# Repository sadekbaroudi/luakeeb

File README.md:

# Pronunciation

Lua Keyboard (luakeeb)

This is a reversible 95mm x 138mm pcb with support for mx switches (no hotswap), per key led, rotary encoders, and exposes the SDA/SCL/GND/VCC lines in the form of the pimoroni trackball pins (meaning you can add that as well, though the case doesn't support it, so you'll need to devise your own mechanism). It also supports the adafruit qwiic connector, so you can add that connector and access I2C (the sda/scl pins) via a standard format!

See https://www.sparkfun.com/qwiic for details

Note that the 6th column can be broken off. The only thing you need to do is (if using per key leds) solder the jumper near the bottom outside of the board, near the mounting hole. You should solder the jumper on the bottom side of the board (if left half, bottom side of the left half, if right half, bottom side of the right half)

# Support me!

I have spent a lot of time and money designing prototypes, testing, developing, etc. Any contributions would be greatly appreciated!

If you don't want to, or can't afford to support me, please send me a message to let me know you've built one, along with pictures. Also, feel free to submit a pull request with pictures into this repository. I'd be happy to showcase your build.

Reddit: /u/sadekbaroudi
Discord: sadekbaroudi#1258

# Cases

## Split case

You can find the split cases here:
https://github.com/sadekbaroudi/luakeeb/tree/master/cases

I only included the left side, since you can use your slicing software to mirror it to 3d print the right side.

## Monoblock support

This keyboard has the exact same layout as the ffkb ( https://github.com/sadekbaroudi/ffkb )

It was designed in such a way that it is perfectly compatible with the ffkb case. The only considerations are:
* The usb port on ffkb is in the center. In this case, you have two (one for each half). You'll need to cut out a spot on each half to allow you to plug it in.
* The trrs jacks need cut outs as well. However, if you don't care about splitting them up, you can solder the halves together instead of using jacks. In the image below, just solder the outer pins to each other, as indicated by the arrows in the image below.

# Firmware

The general folder for the firmware is here:
https://github.com/sadekbaroudi/qmk_firmware/tree/master/keyboards/fingerpunch/luakeeb/

# Pictures

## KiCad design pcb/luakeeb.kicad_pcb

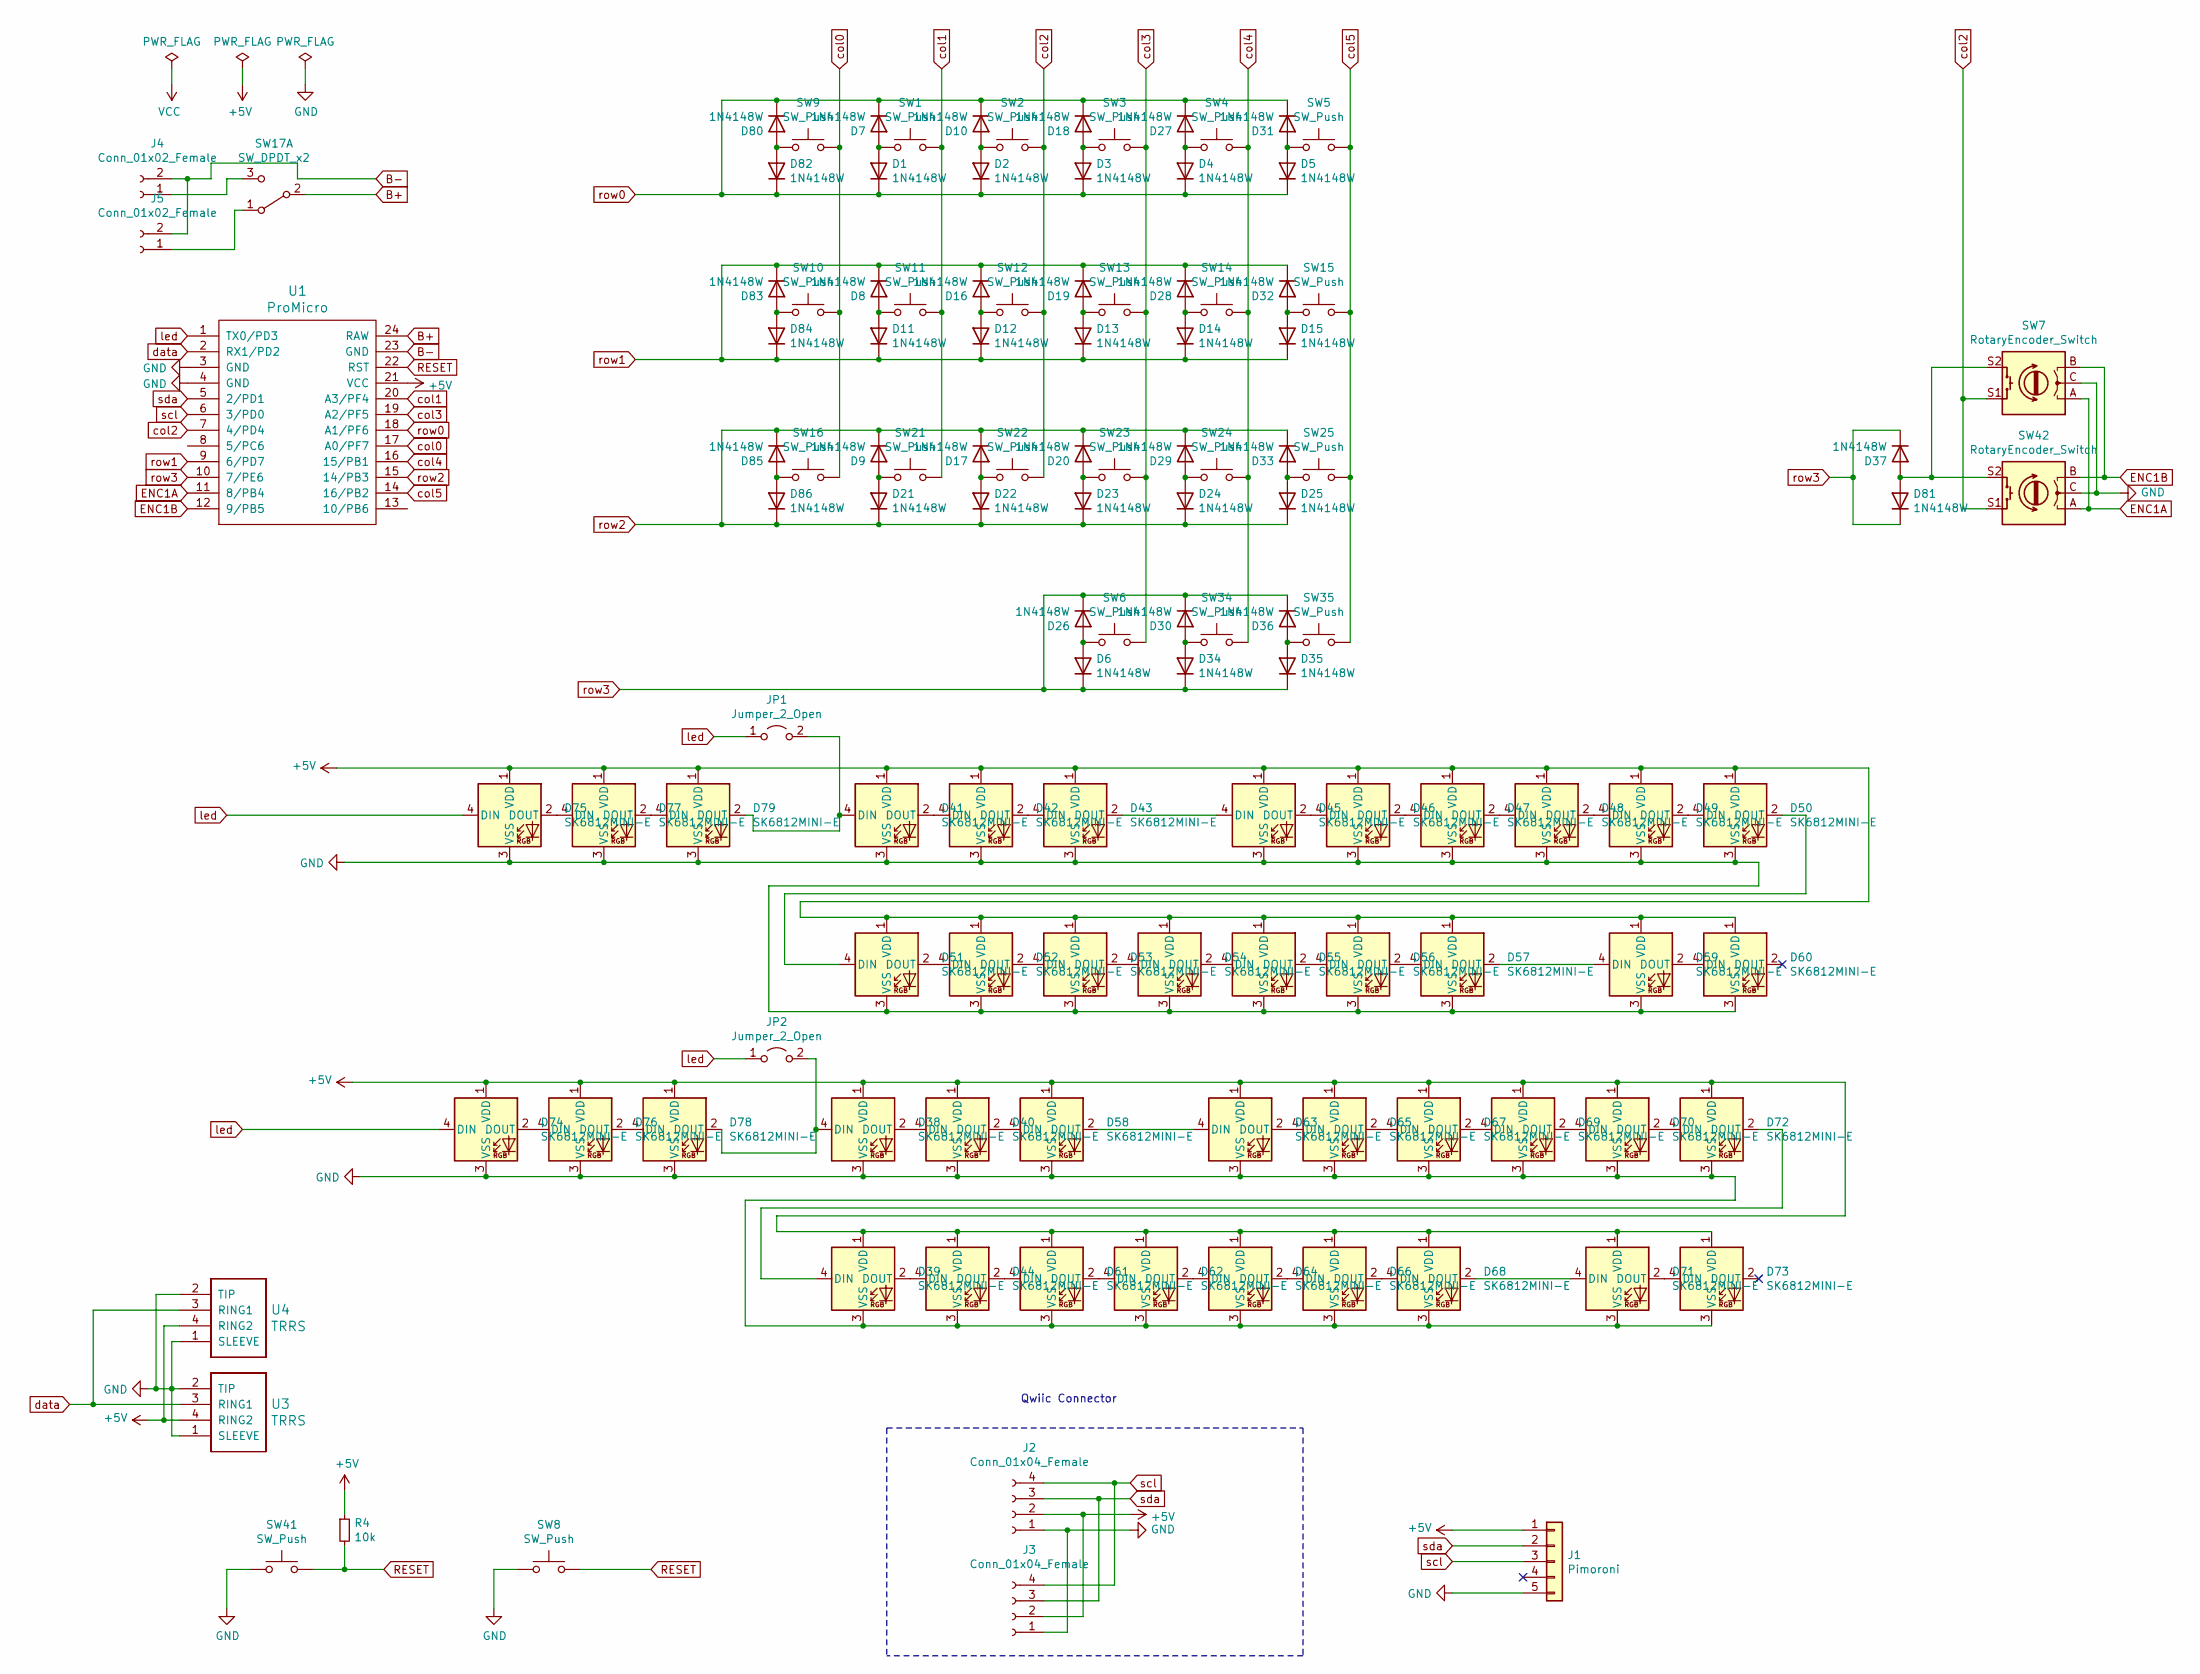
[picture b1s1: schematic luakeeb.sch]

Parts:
D1, D2, D3, D4, D5, D6, D7, D8, D9, D10, D11, D12, D13, D14, D15, D16, D17, D18, D19, D20, D21, D22, D23, D24, D25, D26, D27, D28, D29, D30, D31, D32, D33, D34, D35, D36, D37, D80, D81, D82, D83, D84, D85, D86: 1N4148W; D_SOD-123; LCSC C727110
D38, D39, D40, D41, D42, D43, D44, D45, D46, D47, D48, D49, D50, D51, D52, D53, D54, D55, D56, D57, D58, D59, D60, D61, D62, D63, D64, D65, D66, D67, D68, D69, D70, D71, D72, D73, D74, D75, D76, D77, D78, D79: SK6812MINI-E; MX_SK6812MINI-E
J1: Pimoroni; pimoroni
J2, J3: Conn_01x04_Female; JST_SH_BM04B-SRSS-TB_1x04-1MP_P1.00mm_Vertical
J4, J5: Conn_01x02_Female; JST_PH_S2B-PH-K_1x02_P2.00mm_Horizontal; LCSC C173752
JP1, JP2: Jumper_2_Open; SolderJumper-2_P1.3mm_Open_RoundedPad1.0x1.5mm
R4: 10k; R_0805_2012Metric; LCSC C17414
SW1, SW2, SW3, SW4, SW5, SW6, SW9, SW10, SW11, SW12, SW13, SW14, SW15, SW16, SW21, SW22, SW23, SW24, SW25, SW34, SW35: SW_Push; SW_MX_reversible_minimal
SW7, SW42: RotaryEncoder_Switch; RotaryEncoder_EC11-no-legs
SW8, SW41: SW_Push; SKQG-1155865
SW17: SW_DPDT_x2; SW_CuK_OS102011MA1QN1_SPDT_Angled; LCSC C226259
U1: ProMicro; ArduinoProMicro
U3, U4: TRRS; TRRS-PJ-320A

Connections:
+5V: D38.1 (VDD), D39.1 (VDD), D40.1 (VDD), D41.1 (VDD), D42.1 (VDD), D43.1 (VDD), D44.1 (VDD), D45.1 (VDD), D46.1 (VDD), D47.1 (VDD), D48.1 (VDD), D49.1 (VDD), D50.1 (VDD), D51.1 (VDD), D52.1 (VDD), D53.1 (VDD), D54.1 (VDD), D55.1 (VDD), D56.1 (VDD), D57.1 (VDD), D58.1 (VDD), D59.1 (VDD), D60.1 (VDD), D61.1 (VDD), D62.1 (VDD), D63.1 (VDD), D64.1 (VDD), D65.1 (VDD), D66.1 (VDD), D67.1 (VDD), D68.1 (VDD), D69.1 (VDD), D70.1 (VDD), D71.1 (VDD), D72.1 (VDD), D73.1 (VDD), D74.1 (VDD), D75.1 (VDD), D76.1 (VDD), D77.1 (VDD), D78.1 (VDD), D79.1 (VDD), J1.1, J2.2, J3.2, R4.1, U1.21 (VCC), U3.4 (RING2), U4.4 (RING2)
B+: SW17.2 (B), U1.24 (RAW)
B-: J4.2, J5.2, U1.23 (GND)
ENC1A: SW7.A, SW42.A, U1.11 (8/PB4)
ENC1B: SW7.B, SW42.B, U1.12 (9/PB5)
GND: D38.3 (VSS), D39.3 (VSS), D40.3 (VSS), D41.3 (VSS), D42.3 (VSS), D43.3 (VSS), D44.3 (VSS), D45.3 (VSS), D46.3 (VSS), D47.3 (VSS), D48.3 (VSS), D49.3 (VSS), D50.3 (VSS), D51.3 (VSS), D52.3 (VSS), D53.3 (VSS), D54.3 (VSS), D55.3 (VSS), D56.3 (VSS), D57.3 (VSS), D58.3 (VSS), D59.3 (VSS), D60.3 (VSS), D61.3 (VSS), D62.3 (VSS), D63.3 (VSS), D64.3 (VSS), D65.3 (VSS), D66.3 (VSS), D67.3 (VSS), D68.3 (VSS), D69.3 (VSS), D70.3 (VSS), D71.3 (VSS), D72.3 (VSS), D73.3 (VSS), D74.3 (VSS), D75.3 (VSS), D76.3 (VSS), D77.3 (VSS), D78.3 (VSS), D79.3 (VSS), J1.5, J2.1, J3.1, SW7.C, SW8.1, SW41.1, SW42.C, U1.3 (GND), U1.4 (GND), U3.1 (SLEEVE), U3.2 (TIP), U4.1 (SLEEVE), U4.2 (TIP)
unnamed: D1.2 (A), D7.2 (A), SW1.1
unnamed: D2.2 (A), D10.2 (A), SW2.1
unnamed: D8.2 (A), D11.2 (A), SW11.1
unnamed: D12.2 (A), D16.2 (A), SW12.1
unnamed: D13.2 (A), D19.2 (A), SW13.1
unnamed: D14.2 (A), D28.2 (A), SW14.1
unnamed: D15.2 (A), D32.2 (A), SW15.1
unnamed: D17.2 (A), D22.2 (A), SW22.1
unnamed: D3.2 (A), D18.2 (A), SW3.1
unnamed: D20.2 (A), D23.2 (A), SW23.1
unnamed: D9.2 (A), D21.2 (A), SW21.1
unnamed: D24.2 (A), D29.2 (A), SW24.1
unnamed: D25.2 (A), D33.2 (A), SW25.1
unnamed: D6.2 (A), D26.2 (A), SW6.1
unnamed: D4.2 (A), D27.2 (A), SW4.1
unnamed: D30.2 (A), D34.2 (A), SW34.1
unnamed: D5.2 (A), D31.2 (A), SW5.1
unnamed: D35.2 (A), D36.2 (A), SW35.1
unnamed: D37.2 (A), D81.2 (A), SW7.S2, SW42.S2
unnamed: D38.2 (DOUT), D40.4 (DIN)
unnamed: D38.4 (DIN), D78.2 (DOUT), JP2.2 (B)
unnamed: D39.2 (DOUT), D44.4 (DIN)
unnamed: D39.4 (DIN), D72.2 (DOUT)
unnamed: D40.2 (DOUT), D58.4 (DIN)
unnamed: D41.2 (DOUT), D42.4 (DIN)
unnamed: D41.4 (DIN), D79.2 (DOUT), JP1.2 (B)
unnamed: D42.2 (DOUT), D43.4 (DIN)
unnamed: D43.2 (DOUT), D45.4 (DIN)
unnamed: D44.2 (DOUT), D61.4 (DIN)
unnamed: D45.2 (DOUT), D46.4 (DIN)
unnamed: D46.2 (DOUT), D47.4 (DIN)
unnamed: D47.2 (DOUT), D48.4 (DIN)
unnamed: D48.2 (DOUT), D49.4 (DIN)
unnamed: D49.2 (DOUT), D50.4 (DIN)
unnamed: D50.2 (DOUT), D51.4 (DIN)
unnamed: D51.2 (DOUT), D52.4 (DIN)
unnamed: D52.2 (DOUT), D53.4 (DIN)
unnamed: D53.2 (DOUT), D54.4 (DIN)
unnamed: D54.2 (DOUT), D55.4 (DIN)
unnamed: D55.2 (DOUT), D56.4 (DIN)
unnamed: D56.2 (DOUT), D57.4 (DIN)
unnamed: D57.2 (DOUT), D59.4 (DIN)
unnamed: D58.2 (DOUT), D63.4 (DIN)
unnamed: D59.2 (DOUT), D60.4 (DIN)
unnamed: D61.2 (DOUT), D62.4 (DIN)
unnamed: D62.2 (DOUT), D64.4 (DIN)
unnamed: D63.2 (DOUT), D65.4 (DIN)
unnamed: D64.2 (DOUT), D66.4 (DIN)
unnamed: D65.2 (DOUT), D67.4 (DIN)
unnamed: D66.2 (DOUT), D68.4 (DIN)
unnamed: D67.2 (DOUT), D69.4 (DIN)
unnamed: D68.2 (DOUT), D71.4 (DIN)
unnamed: D69.2 (DOUT), D70.4 (DIN)
unnamed: D70.2 (DOUT), D72.4 (DIN)
unnamed: D71.2 (DOUT), D73.4 (DIN)
unnamed: D74.2 (DOUT), D76.4 (DIN)
unnamed: D75.2 (DOUT), D77.4 (DIN)
unnamed: D76.2 (DOUT), D78.4 (DIN)
unnamed: D77.2 (DOUT), D79.4 (DIN)
unnamed: D80.2 (A), D82.2 (A), SW9.1
unnamed: D83.2 (A), D84.2 (A), SW10.1
unnamed: D85.2 (A), D86.2 (A), SW16.1
unnamed: J4.1, SW17.3 (C)
unnamed: J5.1, SW17.1 (A)
RESET: R4.2, SW8.2, SW41.2, U1.22 (RST)
col0: SW9.2, SW10.2, SW16.2, U1.17 (A0/PF7)
col1: SW1.2, SW11.2, SW21.2, U1.20 (A3/PF4)
col2: SW2.2, SW7.S1, SW12.2, SW22.2, SW42.S1, U1.7 (4/PD4)
col3: SW3.2, SW6.2, SW13.2, SW23.2, U1.19 (A2/PF5)
col4: SW4.2, SW14.2, SW24.2, SW34.2, U1.16 (15/PB1)
col5: SW5.2, SW15.2, SW25.2, SW35.2, U1.14 (16/PB2)
data: U1.2 (RX1/PD2), U3.3 (RING1), U4.3 (RING1)
led: D74.4 (DIN), D75.4 (DIN), JP1.1 (A), JP2.1 (A), U1.1 (TX0/PD3)
row0: D1.1 (K), D2.1 (K), D3.1 (K), D4.1 (K), D5.1 (K), D7.1 (K), D10.1 (K), D18.1 (K), D27.1 (K), D31.1 (K), D80.1 (K), D82.1 (K), U1.18 (A1/PF6)
row1: D8.1 (K), D11.1 (K), D12.1 (K), D13.1 (K), D14.1 (K), D15.1 (K), D16.1 (K), D19.1 (K), D28.1 (K), D32.1 (K), D83.1 (K), D84.1 (K), U1.9 (6/PD7)
row2: D9.1 (K), D17.1 (K), D20.1 (K), D21.1 (K), D22.1 (K), D23.1 (K), D24.1 (K), D25.1 (K), D29.1 (K), D33.1 (K), D85.1 (K), D86.1 (K), U1.15 (14/PB3)
row3: D6.1 (K), D26.1 (K), D30.1 (K), D34.1 (K), D35.1 (K), D36.1 (K), D37.1 (K), D81.1 (K), U1.10 (7/PE6)
scl: J1.3, J2.4, J3.4, U1.6 (3/PD0)
sda: J1.2, J2.3, J3.3, U1.5 (2/PD1)

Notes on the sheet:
Qwiic Connector

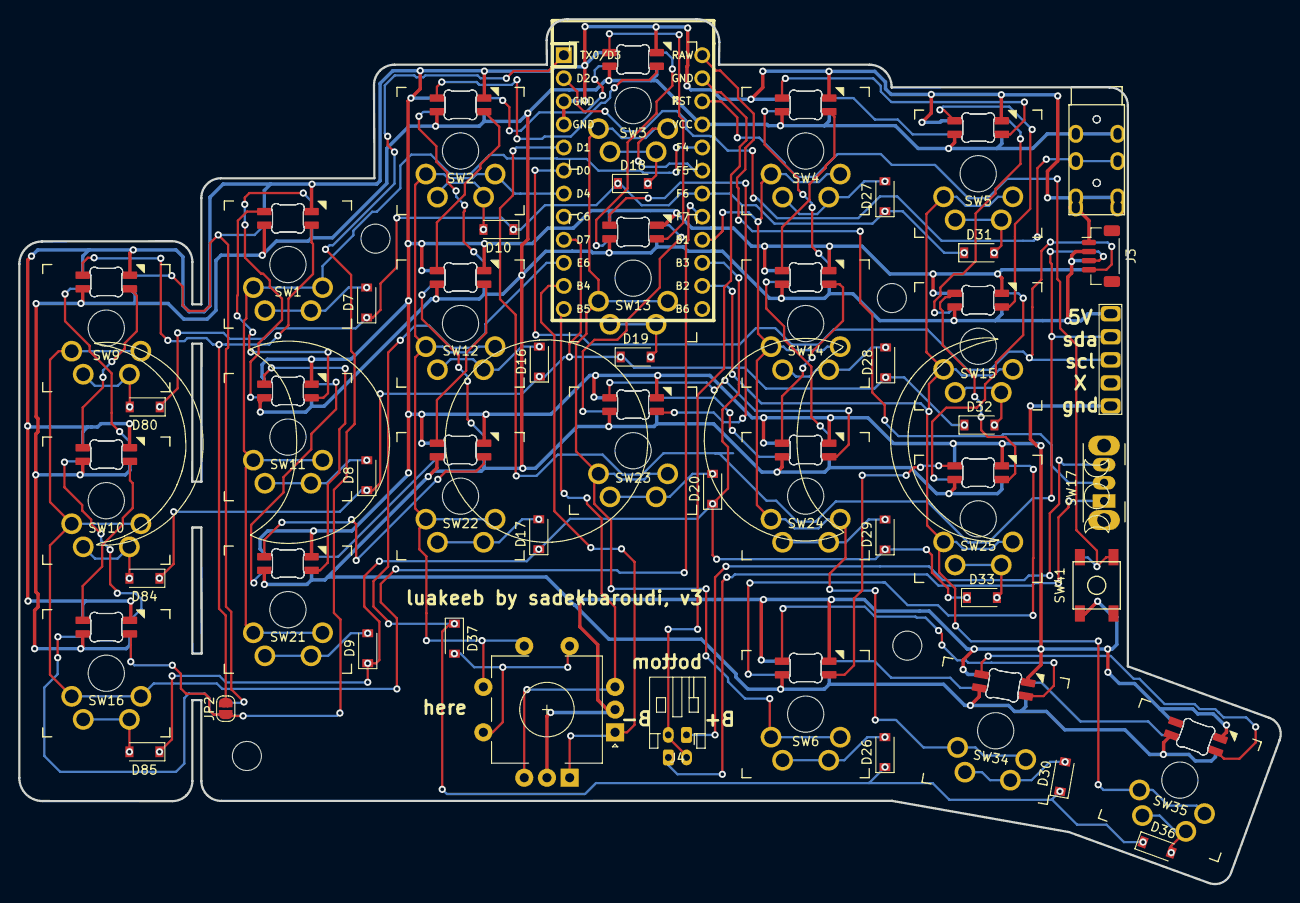
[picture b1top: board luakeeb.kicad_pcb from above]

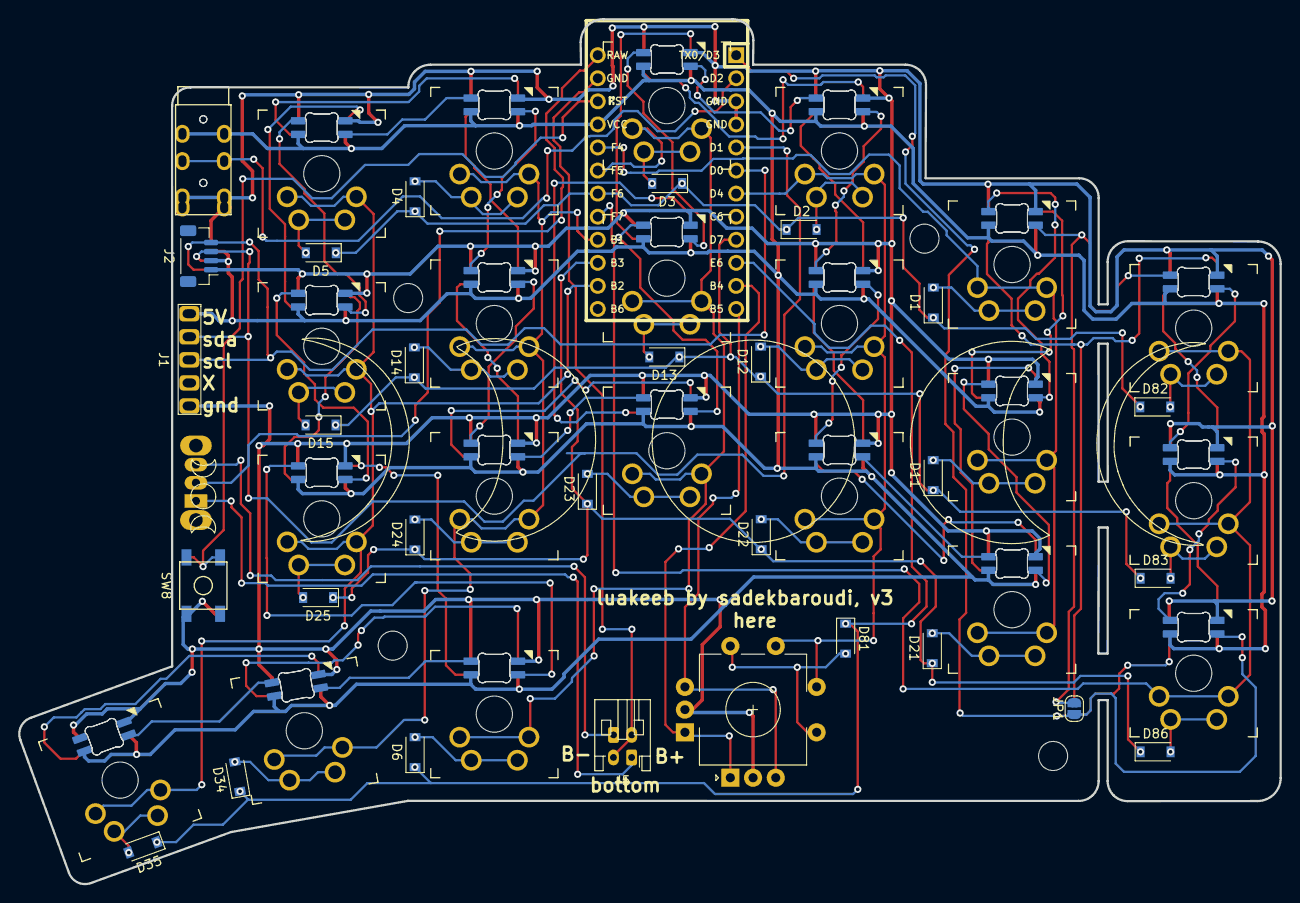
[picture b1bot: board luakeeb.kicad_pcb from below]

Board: 2 copper layers, 138.9 x 95.2 mm, 122 parts (50 on the bottom side), 85 nets.

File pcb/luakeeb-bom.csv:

Comment,Designator,Footprint,LCSC
"1N4148W","D1,D2,D3,D4,D5,D6,D7,D8,D9,D10,D11,D12,D13,D14,D15,D16,D17,D18,D19,D20,D21,D22,D23,D24,D25,D26,D27,D28,D29,D30,D31,D32,D33,D34,D35,D36,D37,D80,D81,D82,D83,D84,D85,D86","Diode_SMD:D_SOD-123","C727110"
"SK6812MINI-E","D38,D39,D40,D41,D42,D43,D44,D45,D46,D47,D48,D49,D50,D51,D52,D53,D54,D55,D56,D57,D58,D59,D60,D61,D62,D63,D64,D65,D66,D67,D68,D69,D70,D71,D72,D73,D74,D75,D76,D77,D78,D79","kicad-keyboard-parts:MX_SK6812MINI-E",""
"Pimoroni","J1","other_parts:pimoroni",""
"Jumper_2_Open","JP1,JP2","Jumper:SolderJumper-2_P1.3mm_Open_RoundedPad1.0x1.5mm",""
"10k","R1,R4","Resistor_SMD:R_0805_2012Metric","C17414"
"SW_Push","SW1,SW2,SW3,SW4,SW5,SW6,SW9,SW10,SW11,SW12,SW13,SW14,SW15,SW16,SW21,SW22,SW23,SW24,SW25,SW34,SW35","keyswitches:SW_MX_reversible_minimal",""
"SW_Push","SW8,SW41","random-keyboard-parts:SKQG-1155865",""
"RotaryEncoder_Switch","SW7,SW42","Keebio-Parts:RotaryEncoder_EC11-no-legs",""
"ProMicro","U1","Keebio-Parts:ArduinoProMicro",""
"TRRS","U3,U4","Keebio-Parts:TRRS-PJ-320A",""

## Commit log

2021-11-27 Lua Keeb initial commit
2021-11-28 added logo svgs and case stls and 3mf files
2021-11-28 added usb port hole to cases
2021-11-30 updated paypal link to direct paypal instead of donation, since they take 29%
2021-12-01 moved encoder a tiny bit to the right, to now match ffkb exactly
2021-12-02 removed the need for separate firmware per half by updating the footprint for the MX switch
2021-12-10 I actually don't know what changed, I must have forgotten to commit, whoops
2021-12-10 added plates for the luakeeb
2021-12-13 added support for the adafruit qwiic connector
2021-12-16 added wireless support for nice nano with wiring, jst connector, and on off switch
2021-12-16 forgot to add the gerber zips for some of the plates
2021-12-28 will use these pogo pin connectors
2022-01-13 updated firmware link to fingerpunch
